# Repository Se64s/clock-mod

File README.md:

# clock-mod

Eurorack clock module based on [Clock](https://freemodular.org/modules/Clock/) from **Free Modular** desing.

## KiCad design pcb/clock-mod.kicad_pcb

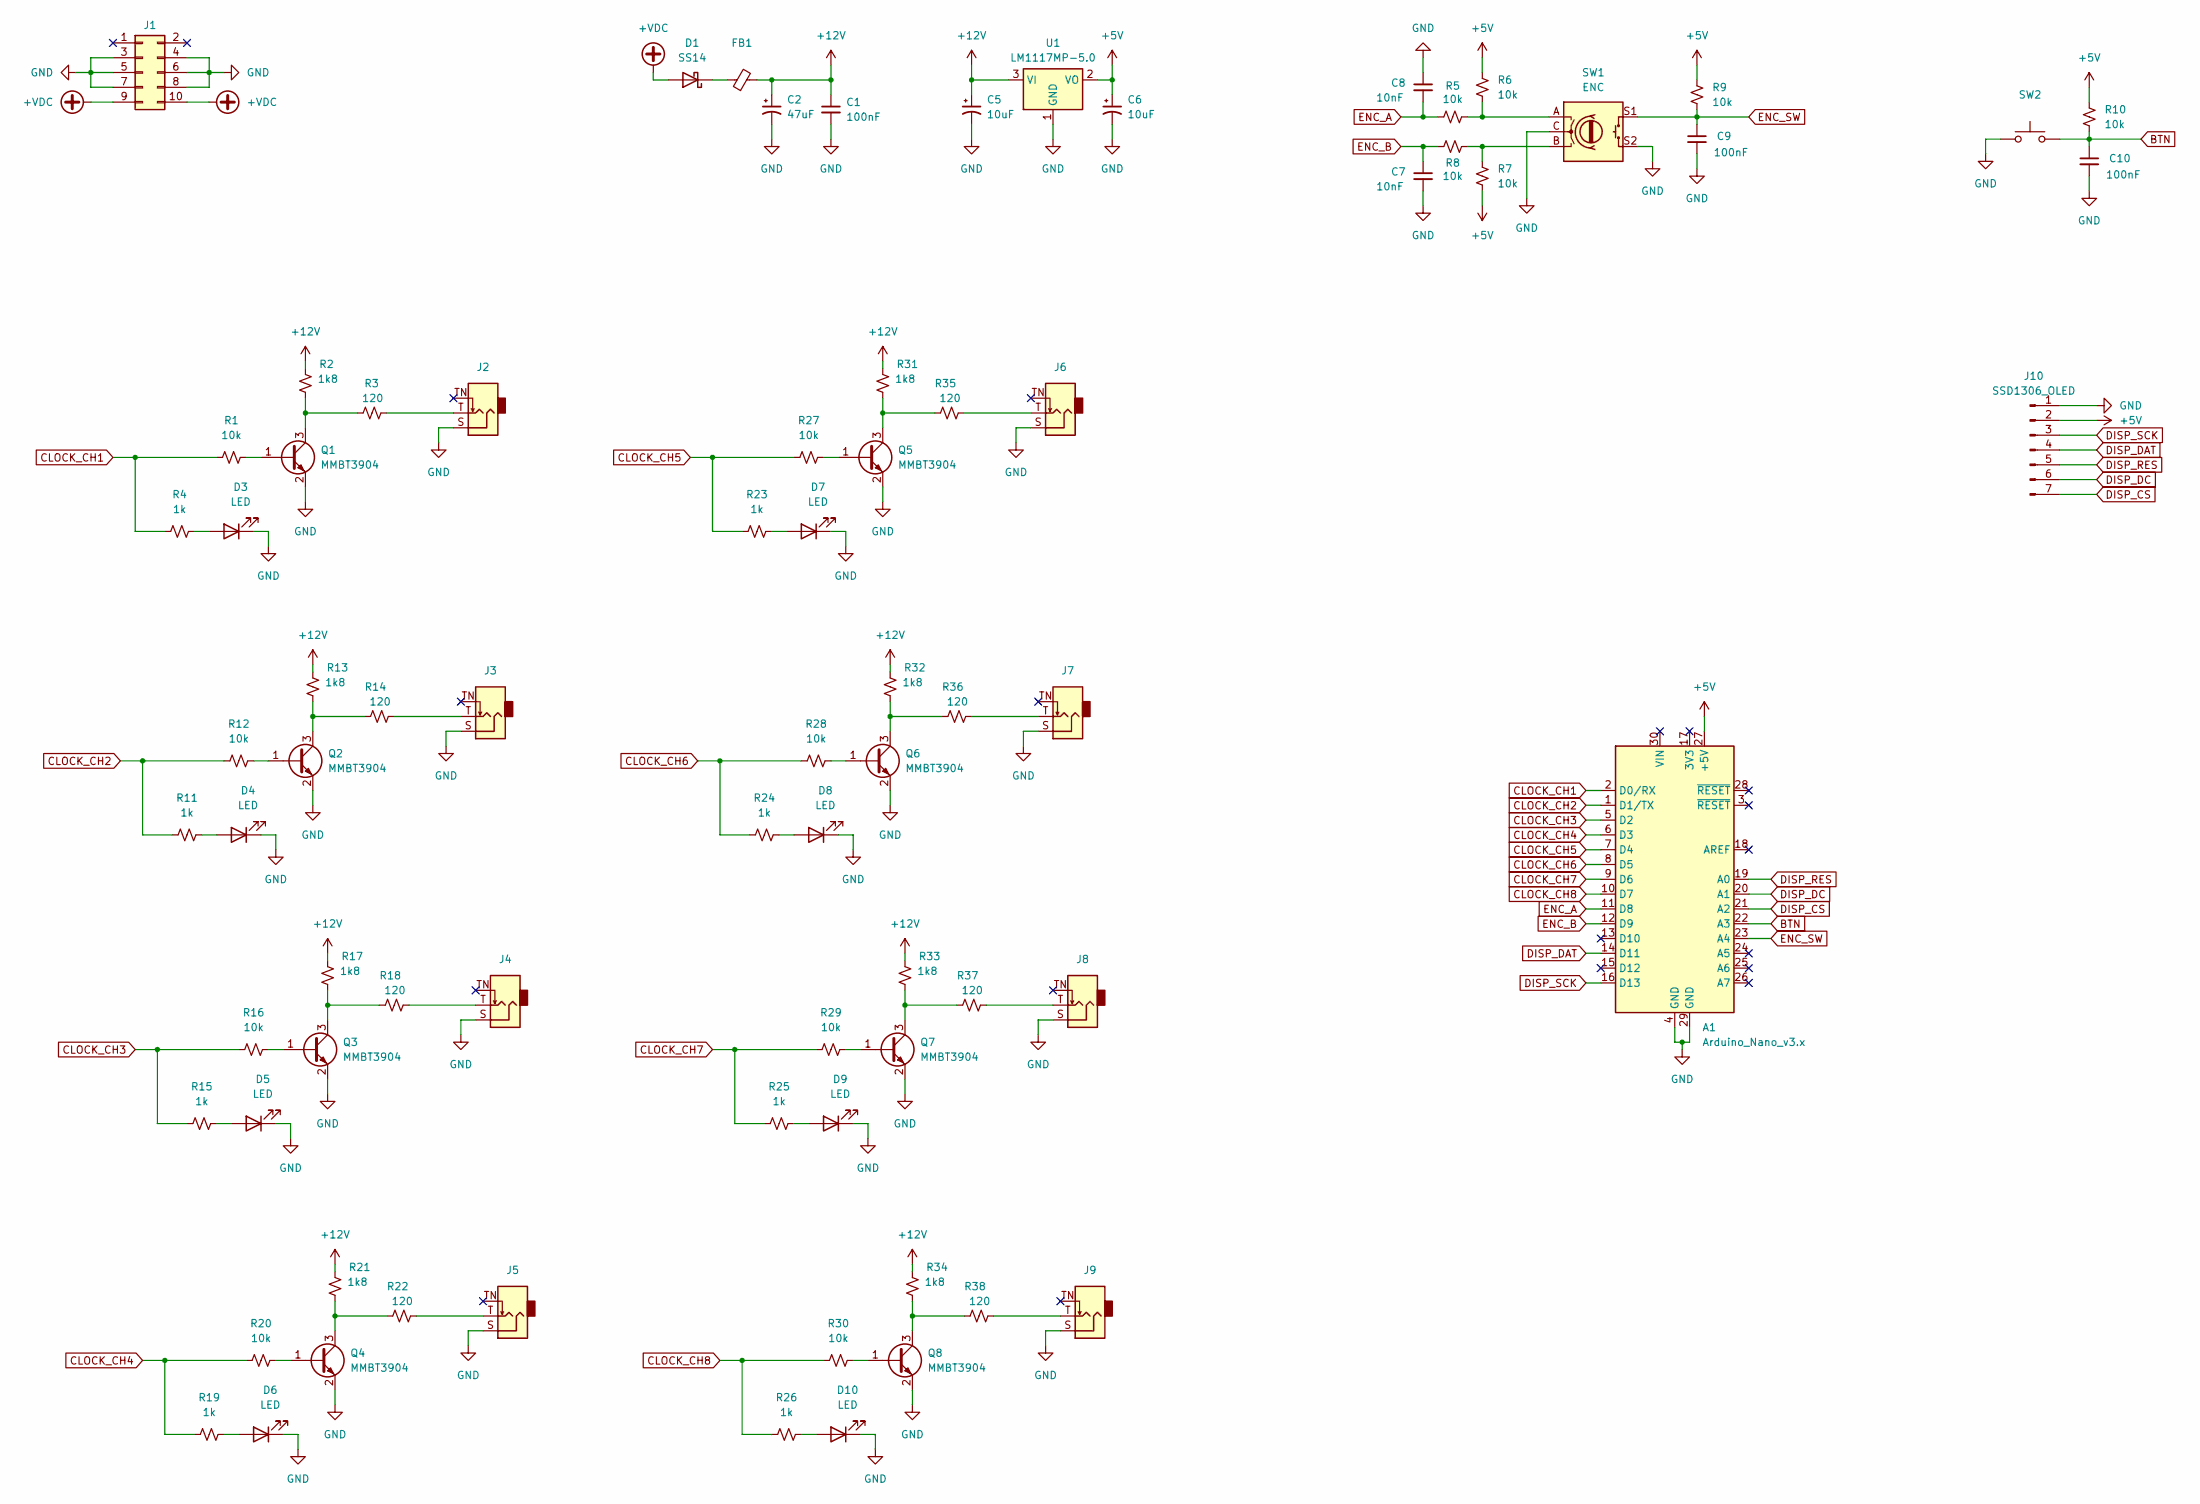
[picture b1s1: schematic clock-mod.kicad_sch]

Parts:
A1: Arduino_Nano_v3.x; Arduino_Nano
C1, C9, C10: 100nF; C_0603_1608Metric_Pad1.08x0.95mm_HandSolder
C2: 47uF; CP_Elec_5x5.4
C5, C6: 10uF; CP_Elec_5x5.4
C7, C8: 10nF; C_0603_1608Metric_Pad1.08x0.95mm_HandSolder
D1: SS14; D_SMA_Handsoldering
D3, D4, D5, D6, D7, D8, D9, D10: LED; LED_D3.0mm
FB1: 1K 100MHz; L_0603_1608Metric_Pad1.05x0.95mm_HandSolder
J1: POWER; IDC-Header_2x05_P2.54mm_Vertical_SMD
J2, J3, J4, J5, J6, J7, J8, J9: AudioJack2_SwitchT; Jack_3.5mm_QingPu_WQP-PJ398SM_Vertical_CircularHoles
J10: SSD1306_OLED; PinHeader_1x07_P2.54mm_Vertical
Q1, Q2, Q3, Q4, Q5, Q6, Q7, Q8: MMBT3904; SOT-23_Handsoldering
R1, R5, R6, R7, R8, R9, R10, R12, R16, R20, R27, R28, R29, R30: 10k; R_0603_1608Metric_Pad0.98x0.95mm_HandSolder
R2, R13, R17, R21, R31, R32, R33, R34: 1k8; R_0603_1608Metric_Pad0.98x0.95mm_HandSolder
R3, R14, R18, R22, R35, R36, R37, R38: 120; R_0603_1608Metric_Pad0.98x0.95mm_HandSolder
R4, R11, R15, R19, R23, R24, R25, R26: 1k; R_0603_1608Metric_Pad0.98x0.95mm_HandSolder
SW1: ENC; RotaryEncoder_Alps_EC11E-Switch_Vertical_H20mm
SW2: SW_Push; SW_PUSH-12mm
U1: LM1117MP-5.0; SOT-223-3_TabPin2

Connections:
+5V: A1.27 (+5V), C6.1, J10.2, R6.2, R7.1, R9.2, R10.2, U1.2 (VO)
+12V: C1.1, C2.1, C5.1, FB1.2, R2.2, R13.2, R17.2, R21.2, R31.2, R32.2, R33.2, R34.2, U1.3 (VI)
+VDC: D1.2 (A), J1.9, J1.10
BTN: A1.22 (A3), C10.1, R10.1, SW2.2
CLOCK_CH1: A1.2 (D0/RX), R1.1, R4.1
CLOCK_CH2: A1.1 (D1/TX), R11.1, R12.1
CLOCK_CH3: A1.5 (D2), R15.1, R16.1
CLOCK_CH4: A1.6 (D3), R19.1, R20.1
CLOCK_CH5: A1.7 (D4), R23.1, R27.1
CLOCK_CH6: A1.8 (D5), R24.1, R28.1
CLOCK_CH7: A1.9 (D6), R25.1, R29.1
CLOCK_CH8: A1.10 (D7), R26.1, R30.1
DISP_CS: A1.21 (A2), J10.7
DISP_DAT: A1.14 (D11), J10.4
DISP_DC: A1.20 (A1), J10.6
DISP_RES: A1.19 (A0), J10.5
DISP_SCK: A1.16 (D13), J10.3
ENC_A: A1.11 (D8), C8.2, R5.1
ENC_B: A1.12 (D9), C7.1, R8.2
ENC_SW: A1.23 (A4), C9.1, R9.1, SW1.S1
GND: A1.4 (GND), A1.29 (GND), C1.2, C2.2, C5.2, C6.2, C7.2, C8.1, C9.2, C10.2, D3.1 (K), D4.1 (K), D5.1 (K), D6.1 (K), D7.1 (K), D8.1 (K), D9.1 (K), D10.1 (K), J1.3, J1.4, J1.5, J1.6, J1.7, J1.8, J2.S, J3.S, J4.S, J5.S, J6.S, J7.S, J8.S, J9.S, J10.1, Q1.2 (E), Q2.2 (E), Q3.2 (E), Q4.2 (E), Q5.2 (E), Q6.2 (E), Q7.2 (E), Q8.2 (E), SW1.C, SW1.S2, SW2.1, U1.1 (GND)
unnamed: D1.1 (K), FB1.1
unnamed: D3.2 (A), R4.2
unnamed: D4.2 (A), R11.2
unnamed: D5.2 (A), R15.2
unnamed: D6.2 (A), R19.2
unnamed: D7.2 (A), R23.2
unnamed: D8.2 (A), R24.2
unnamed: D9.2 (A), R25.2
unnamed: D10.2 (A), R26.2
unnamed: J2.T, R3.1
unnamed: J3.T, R14.1
unnamed: J4.T, R18.1
unnamed: J5.T, R22.1
unnamed: J6.T, R35.1
unnamed: J7.T, R36.1
unnamed: J8.T, R37.1
unnamed: J9.T, R38.1
unnamed: Q1.1 (B), R1.2
unnamed: Q1.3 (C), R2.1, R3.2
unnamed: Q2.1 (B), R12.2
unnamed: Q2.3 (C), R13.1, R14.2
unnamed: Q3.1 (B), R16.2
unnamed: Q3.3 (C), R17.1, R18.2
unnamed: Q4.1 (B), R20.2
unnamed: Q4.3 (C), R21.1, R22.2
unnamed: Q5.1 (B), R27.2
unnamed: Q5.3 (C), R31.1, R35.2
unnamed: Q6.1 (B), R28.2
unnamed: Q6.3 (C), R32.1, R36.2
unnamed: Q7.1 (B), R29.2
unnamed: Q7.3 (C), R33.1, R37.2
unnamed: Q8.1 (B), R30.2
unnamed: Q8.3 (C), R34.1, R38.2
unnamed: R5.2, R6.1, SW1.A
unnamed: R7.2, R8.1, SW1.B

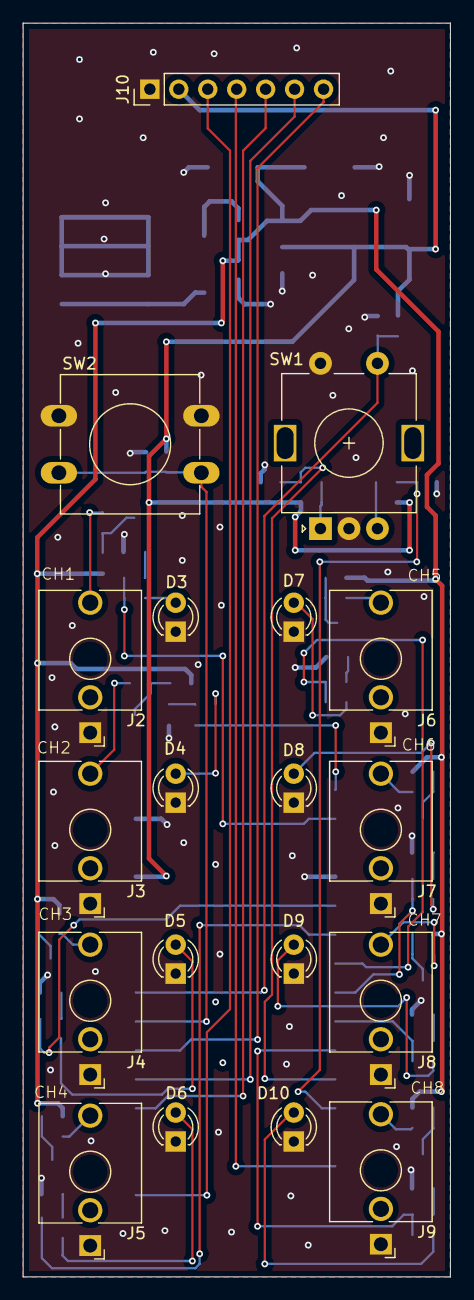
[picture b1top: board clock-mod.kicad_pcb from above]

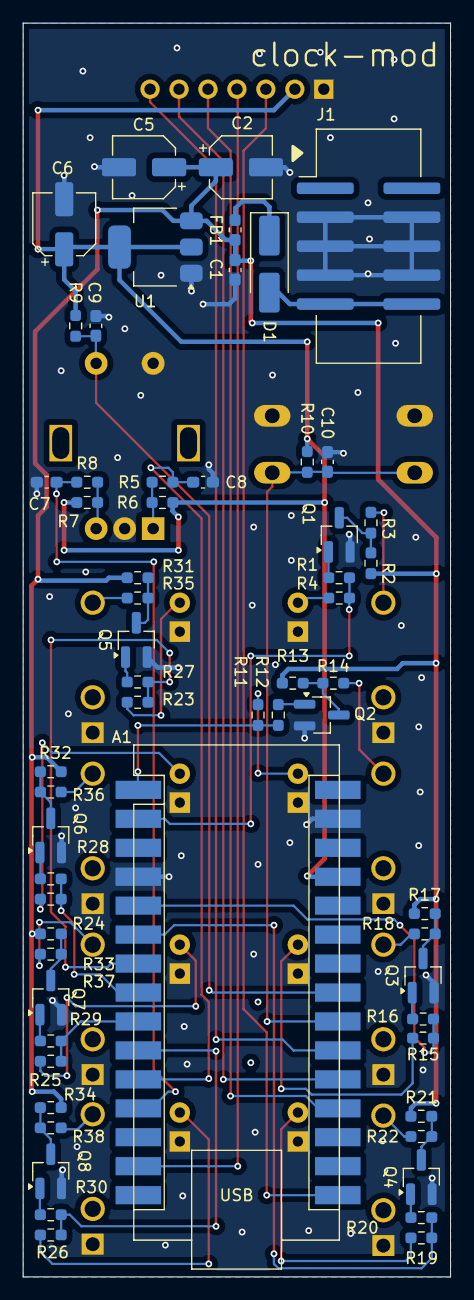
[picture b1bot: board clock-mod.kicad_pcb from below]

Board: 2 copper layers, 37.5 x 110.0 mm, 78 parts (59 on the bottom side), 56 nets.

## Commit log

2025-09-14 git: extend ignore files
2025-09-16 feat: pcb layout complete
2025-09-16 feat: panel base
2025-09-16 feat: add artwork to panel
2025-09-16 doc: update readme with design origin
2025-10-06 git: exclude fab output folder from gitlab
2025-10-06 proj: add config for gerber generation for jlcpcb
2025-10-06 proj: add config to generate bom
